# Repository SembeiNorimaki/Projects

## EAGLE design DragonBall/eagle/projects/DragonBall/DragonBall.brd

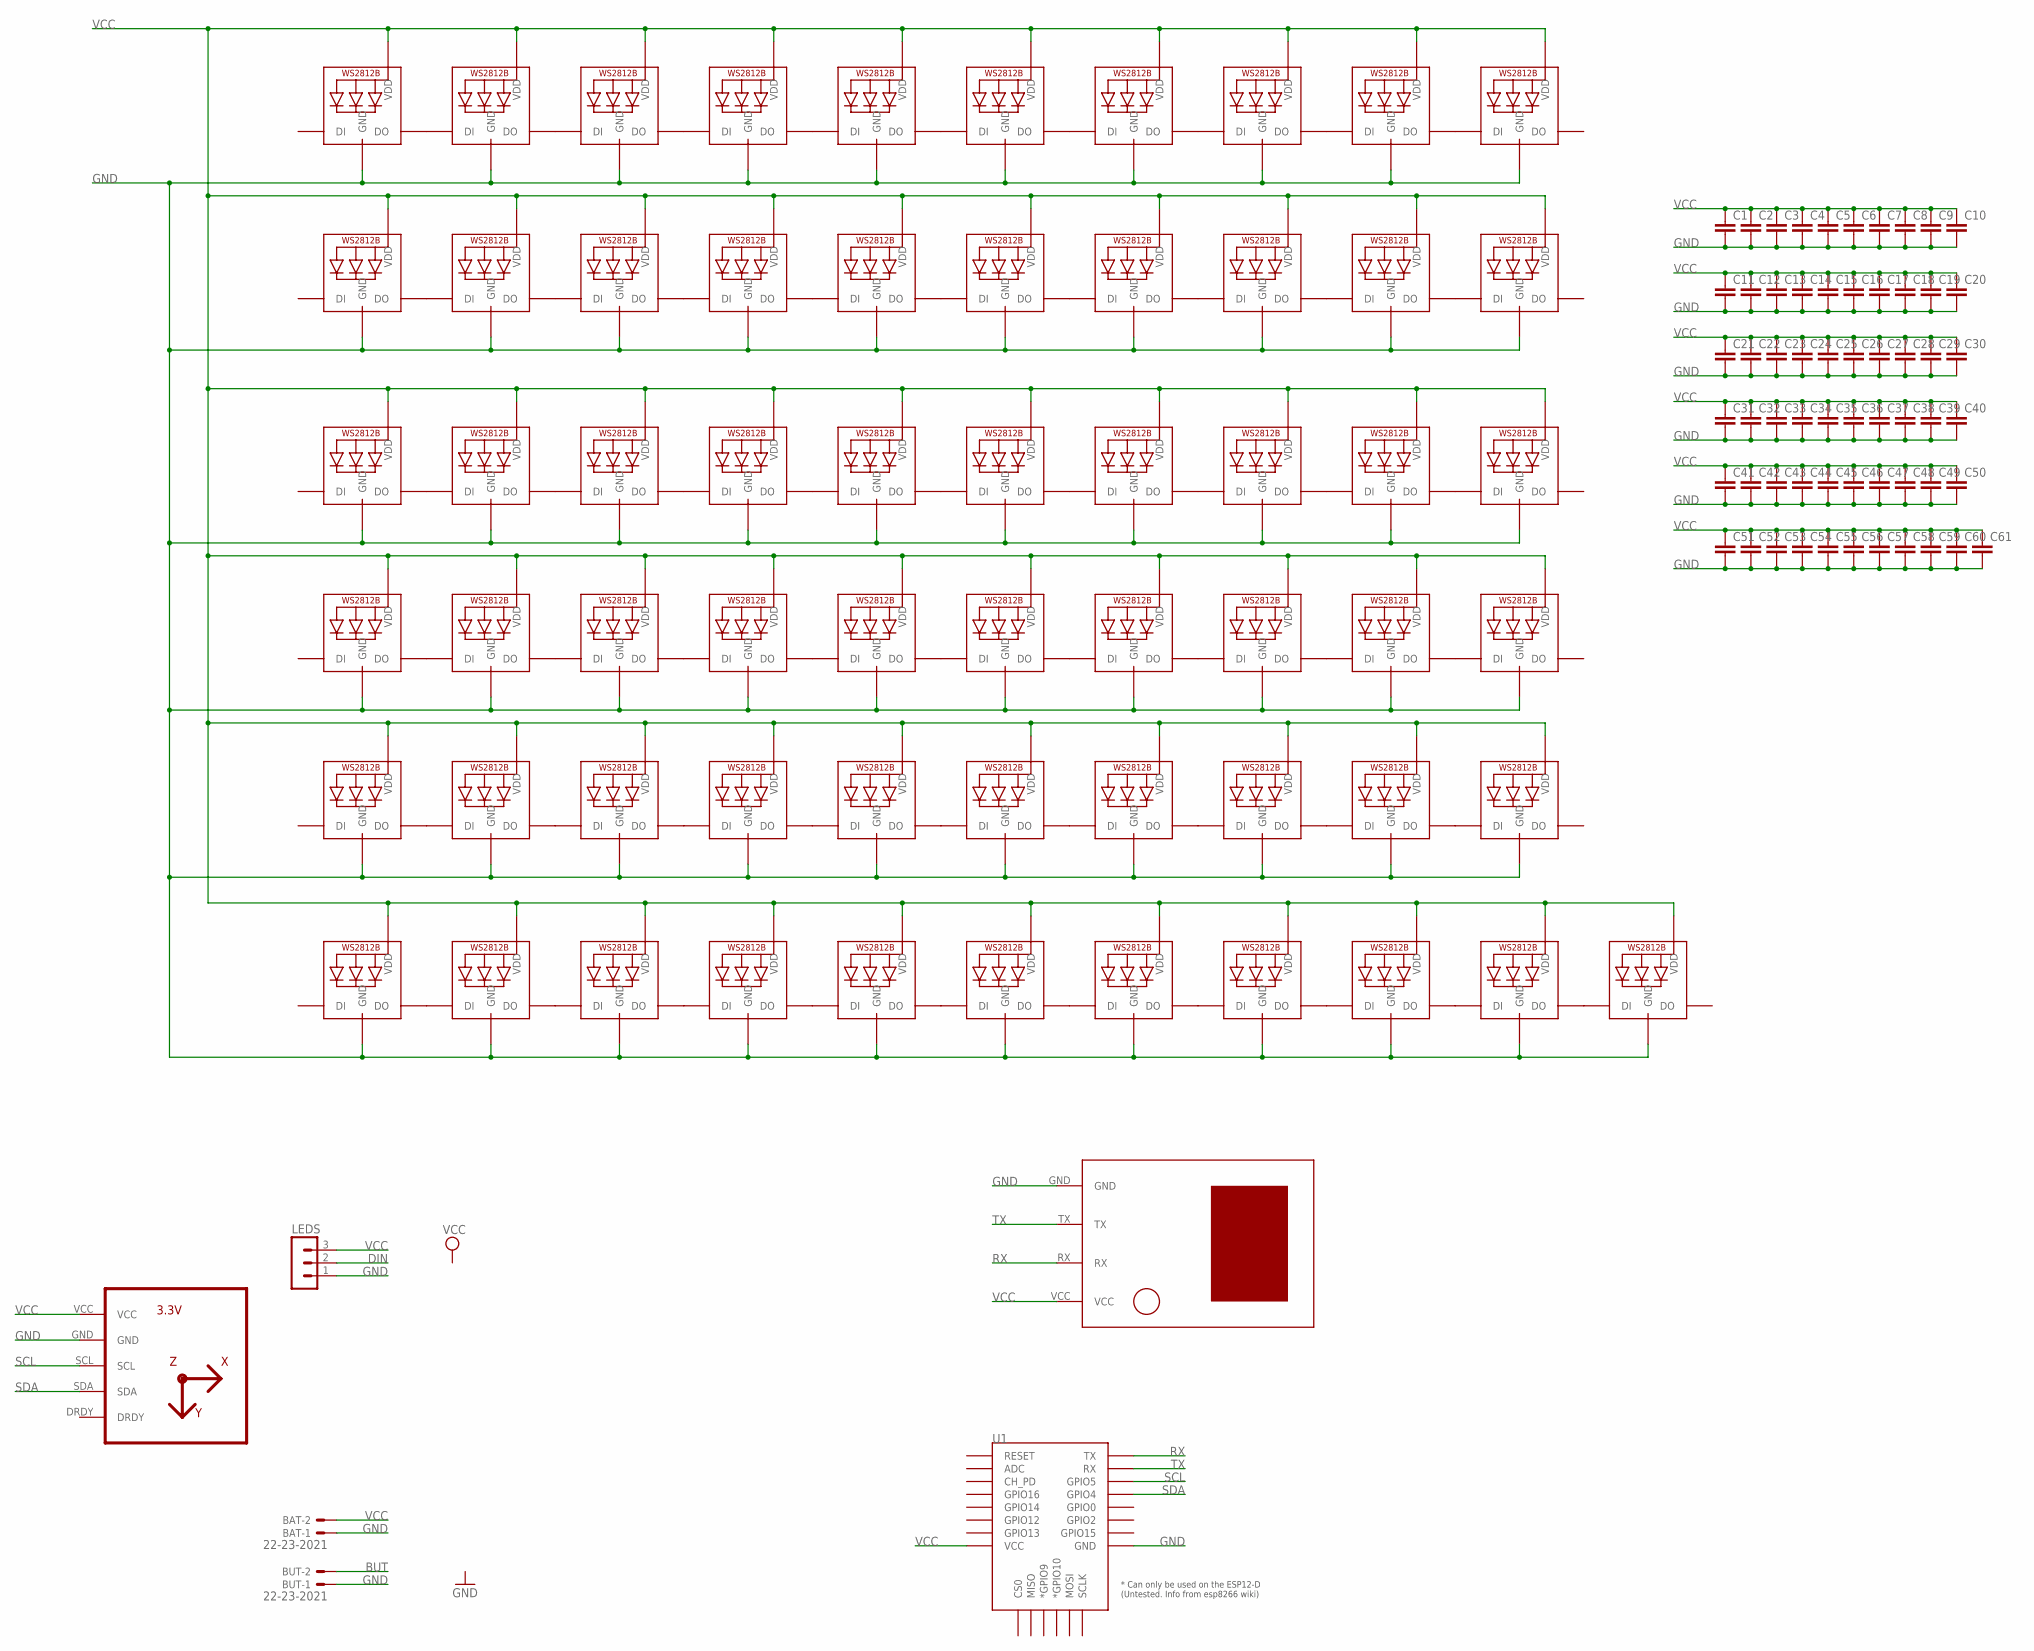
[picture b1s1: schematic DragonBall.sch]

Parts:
BAT: 22-23-2021
BUT: 22-23-2021
C1, C2, C3, C4, C5, C6, C7, C8, C9, C10, C11, C12, C13, C14, C15, C16, C17, C18, C19, C20, C21, C22, C23, C24, C25, C26, C27, C28, C29, C30, C31, C32, C33, C34, C35, C36, C37, C38, C39, C40, C41, C42, C43, C44, C45, C46, C47, C48, C49, C50, C51, C52, C53, C54, C55, C56, C57, C58, C59, C60, C61: C-EUC0402K; C0402K
GYRO: HMC5883LGY-271; GY-271
LED1, LED2, LED3, LED4, LED5, LED6, LED7, LED8, LED9, LED10, LED11, LED12, LED13, LED14, LED15, LED16, LED17, LED18, LED19, LED20, LED21, LED22, LED23, LED24, LED25, LED26, LED27, LED28, LED29, LED30, LED31, LED32, LED33, LED34, LED35, LED36, LED37, LED38, LED39, LED40, LED41, LED42, LED43, LED44, LED45, LED46, LED47, LED48, LED49, LED50, LED51, LED52, LED53, LED54, LED55, LED56, LED57, LED58, LED59, LED60, LED61: WS2812B_5050N; WS2812B-NARROW
LEDS: MA03-1
U1: ESP12ESMD; ESP12E-SMD
U$3: U-BLOX-NEO6V2

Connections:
BUT: BUT.2
DIN: LEDS.2
GND: BAT.1, BUT.1, C1.2, C2.2, C3.2, C4.2, C5.2, C6.2, C7.2, C8.2, C9.2, C10.2, C11.2, C12.2, C13.2, C14.2, C15.2, C16.2, C17.2, C18.2, C19.2, C20.2, C21.2, C22.2, C23.2, C24.2, C25.2, C26.2, C27.2, C28.2, C29.2, C30.2, C31.2, C32.2, C33.2, C34.2, C35.2, C36.2, C37.2, C38.2, C39.2, C40.2, C41.2, C42.2, C43.2, C44.2, C45.2, C46.2, C47.2, C48.2, C49.2, C50.2, C51.2, C52.2, C53.2, C54.2, C55.2, C56.2, C57.2, C58.2, C59.2, C60.2, C61.2, GYRO.GND, LED1.3-GND (GND), LED2.3-GND (GND), LED3.3-GND (GND), LED4.3-GND (GND), LED5.3-GND (GND), LED6.3-GND (GND), LED7.3-GND (GND), LED8.3-GND (GND), LED9.3-GND (GND), LED10.3-GND (GND), LED11.3-GND (GND), LED12.3-GND (GND), LED13.3-GND (GND), LED14.3-GND (GND), LED15.3-GND (GND), LED16.3-GND (GND), LED17.3-GND (GND), LED18.3-GND (GND), LED19.3-GND (GND), LED20.3-GND (GND), LED21.3-GND (GND), LED22.3-GND (GND), LED23.3-GND (GND), LED24.3-GND (GND), LED25.3-GND (GND), LED26.3-GND (GND), LED27.3-GND (GND), LED28.3-GND (GND), LED29.3-GND (GND), LED30.3-GND (GND), LED31.3-GND (GND), LED32.3-GND (GND), LED33.3-GND (GND), LED34.3-GND (GND), LED35.3-GND (GND), LED36.3-GND (GND), LED37.3-GND (GND), LED38.3-GND (GND), LED39.3-GND (GND), LED40.3-GND (GND), LED41.3-GND (GND), LED42.3-GND (GND), LED43.3-GND (GND), LED44.3-GND (GND), LED45.3-GND (GND), LED46.3-GND (GND), LED47.3-GND (GND), LED48.3-GND (GND), LED49.3-GND (GND), LED50.3-GND (GND), LED51.3-GND (GND), LED52.3-GND (GND), LED53.3-GND (GND), LED54.3-GND (GND), LED55.3-GND (GND), LED56.3-GND (GND), LED57.3-GND (GND), LED58.3-GND (GND), LED59.3-GND (GND), LED60.3-GND (GND), LED61.3-GND (GND), LEDS.1, U1.GND, U$3.GND
unnamed: LED1.2-DOUT (DO), LED2.4-DIN (DI)
unnamed: LED2.2-DOUT (DO), LED3.4-DIN (DI)
unnamed: LED3.2-DOUT (DO), LED4.4-DIN (DI)
unnamed: LED4.2-DOUT (DO), LED5.4-DIN (DI)
unnamed: LED5.2-DOUT (DO), LED6.4-DIN (DI)
unnamed: LED6.2-DOUT (DO), LED7.4-DIN (DI)
unnamed: LED7.2-DOUT (DO), LED8.4-DIN (DI)
unnamed: LED8.2-DOUT (DO), LED9.4-DIN (DI)
unnamed: LED9.2-DOUT (DO), LED10.4-DIN (DI)
unnamed: LED11.2-DOUT (DO), LED12.4-DIN (DI)
unnamed: LED12.2-DOUT (DO), LED13.4-DIN (DI)
unnamed: LED13.2-DOUT (DO), LED14.4-DIN (DI)
unnamed: LED14.2-DOUT (DO), LED15.4-DIN (DI)
unnamed: LED15.2-DOUT (DO), LED16.4-DIN (DI)
unnamed: LED16.2-DOUT (DO), LED17.4-DIN (DI)
unnamed: LED17.2-DOUT (DO), LED18.4-DIN (DI)
unnamed: LED18.2-DOUT (DO), LED19.4-DIN (DI)
unnamed: LED19.2-DOUT (DO), LED20.4-DIN (DI)
unnamed: LED21.2-DOUT (DO), LED22.4-DIN (DI)
unnamed: LED22.2-DOUT (DO), LED23.4-DIN (DI)
unnamed: LED23.2-DOUT (DO), LED24.4-DIN (DI)
unnamed: LED24.2-DOUT (DO), LED25.4-DIN (DI)
unnamed: LED25.2-DOUT (DO), LED26.4-DIN (DI)
unnamed: LED26.2-DOUT (DO), LED27.4-DIN (DI)
unnamed: LED27.2-DOUT (DO), LED28.4-DIN (DI)
unnamed: LED28.2-DOUT (DO), LED29.4-DIN (DI)
unnamed: LED29.2-DOUT (DO), LED30.4-DIN (DI)
unnamed: LED31.2-DOUT (DO), LED32.4-DIN (DI)
unnamed: LED32.2-DOUT (DO), LED33.4-DIN (DI)
unnamed: LED33.2-DOUT (DO), LED34.4-DIN (DI)
unnamed: LED34.2-DOUT (DO), LED35.4-DIN (DI)
unnamed: LED35.2-DOUT (DO), LED36.4-DIN (DI)
unnamed: LED36.2-DOUT (DO), LED37.4-DIN (DI)
unnamed: LED37.2-DOUT (DO), LED38.4-DIN (DI)
unnamed: LED38.2-DOUT (DO), LED39.4-DIN (DI)
unnamed: LED39.2-DOUT (DO), LED40.4-DIN (DI)
unnamed: LED41.2-DOUT (DO), LED42.4-DIN (DI)
unnamed: LED42.2-DOUT (DO), LED43.4-DIN (DI)
unnamed: LED43.2-DOUT (DO), LED44.4-DIN (DI)
unnamed: LED44.2-DOUT (DO), LED45.4-DIN (DI)
unnamed: LED45.2-DOUT (DO), LED46.4-DIN (DI)
unnamed: LED46.2-DOUT (DO), LED47.4-DIN (DI)
unnamed: LED47.2-DOUT (DO), LED48.4-DIN (DI)
unnamed: LED48.2-DOUT (DO), LED49.4-DIN (DI)
unnamed: LED49.2-DOUT (DO), LED50.4-DIN (DI)
unnamed: LED51.2-DOUT (DO), LED52.4-DIN (DI)
unnamed: LED52.2-DOUT (DO), LED53.4-DIN (DI)
unnamed: LED53.2-DOUT (DO), LED54.4-DIN (DI)
unnamed: LED54.2-DOUT (DO), LED55.4-DIN (DI)
unnamed: LED55.2-DOUT (DO), LED56.4-DIN (DI)
unnamed: LED56.2-DOUT (DO), LED57.4-DIN (DI)
unnamed: LED57.2-DOUT (DO), LED58.4-DIN (DI)
unnamed: LED58.2-DOUT (DO), LED59.4-DIN (DI)
unnamed: LED59.2-DOUT (DO), LED60.4-DIN (DI)
unnamed: LED60.2-DOUT (DO), LED61.4-DIN (DI)
RX: U1.TXD0 (TX), U$3.RX
SCL: GYRO.SCL, U1.GPIO5
SDA: GYRO.SDA, U1.GPIO4
TX: U1.RXD0 (RX), U$3.TX
VCC: BAT.2, C1.1, C2.1, C3.1, C4.1, C5.1, C6.1, C7.1, C8.1, C9.1, C10.1, C11.1, C12.1, C13.1, C14.1, C15.1, C16.1, C17.1, C18.1, C19.1, C20.1, C21.1, C22.1, C23.1, C24.1, C25.1, C26.1, C27.1, C28.1, C29.1, C30.1, C31.1, C32.1, C33.1, C34.1, C35.1, C36.1, C37.1, C38.1, C39.1, C40.1, C41.1, C42.1, C43.1, C44.1, C45.1, C46.1, C47.1, C48.1, C49.1, C50.1, C51.1, C52.1, C53.1, C54.1, C55.1, C56.1, C57.1, C58.1, C59.1, C60.1, C61.1, GYRO.VCC, LED1.1-VDD (VDD), LED2.1-VDD (VDD), LED3.1-VDD (VDD), LED4.1-VDD (VDD), LED5.1-VDD (VDD), LED6.1-VDD (VDD), LED7.1-VDD (VDD), LED8.1-VDD (VDD), LED9.1-VDD (VDD), LED10.1-VDD (VDD), LED11.1-VDD (VDD), LED12.1-VDD (VDD), LED13.1-VDD (VDD), LED14.1-VDD (VDD), LED15.1-VDD (VDD), LED16.1-VDD (VDD), LED17.1-VDD (VDD), LED18.1-VDD (VDD), LED19.1-VDD (VDD), LED20.1-VDD (VDD), LED21.1-VDD (VDD), LED22.1-VDD (VDD), LED23.1-VDD (VDD), LED24.1-VDD (VDD), LED25.1-VDD (VDD), LED26.1-VDD (VDD), LED27.1-VDD (VDD), LED28.1-VDD (VDD), LED29.1-VDD (VDD), LED30.1-VDD (VDD), LED31.1-VDD (VDD), LED32.1-VDD (VDD), LED33.1-VDD (VDD), LED34.1-VDD (VDD), LED35.1-VDD (VDD), LED36.1-VDD (VDD), LED37.1-VDD (VDD), LED38.1-VDD (VDD), LED39.1-VDD (VDD), LED40.1-VDD (VDD), LED41.1-VDD (VDD), LED42.1-VDD (VDD), LED43.1-VDD (VDD), LED44.1-VDD (VDD), LED45.1-VDD (VDD), LED46.1-VDD (VDD), LED47.1-VDD (VDD), LED48.1-VDD (VDD), LED49.1-VDD (VDD), LED50.1-VDD (VDD), LED51.1-VDD (VDD), LED52.1-VDD (VDD), LED53.1-VDD (VDD), LED54.1-VDD (VDD), LED55.1-VDD (VDD), LED56.1-VDD (VDD), LED57.1-VDD (VDD), LED58.1-VDD (VDD), LED59.1-VDD (VDD), LED60.1-VDD (VDD), LED61.1-VDD (VDD), LEDS.3, U1.VCC, U$3.VCC

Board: 2 copper layers, 128 parts (3 on the bottom side), 61 nets, no tracks yet.

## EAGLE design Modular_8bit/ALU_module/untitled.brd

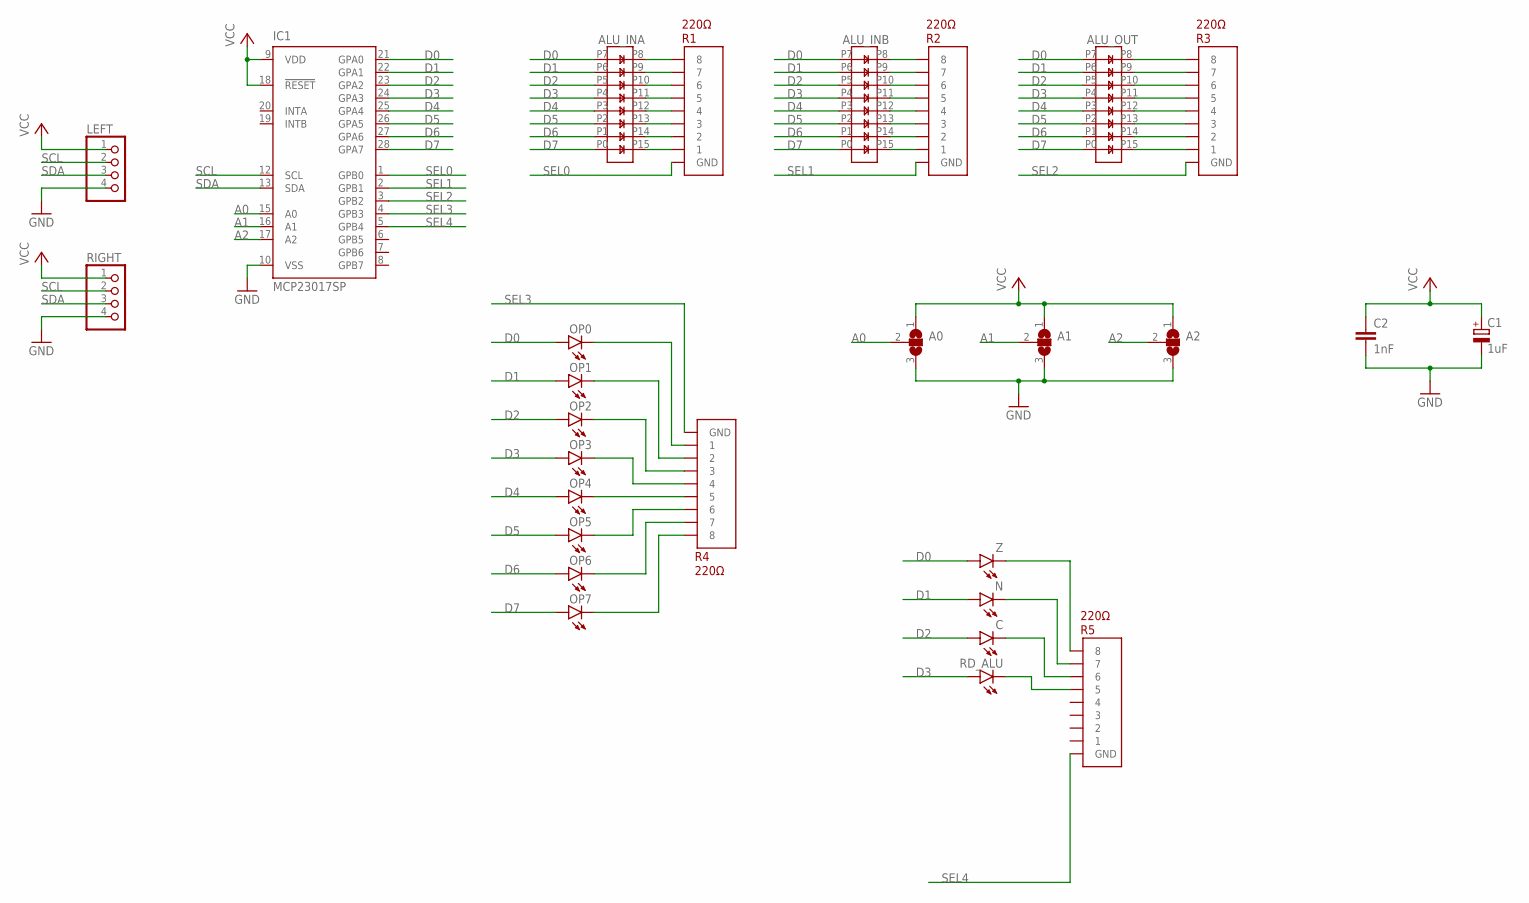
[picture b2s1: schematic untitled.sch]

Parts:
A0, A1, A2: SJ2W; SJ_2
ALU_INA: LB8
ALU_INB: LB8
ALU_OUT: LB8
C: LED3MM
C1: 1uF; E2,5-6
C2: 1nF; C2.5-2
IC1: MCP23017SP; DIL28-3
LEFT: PINHD-1X4; 1X04
N: LED3MM
OP0, OP1, OP2, OP3, OP4, OP5, OP6, OP7: LED3MM
R1, R2, R3, R4, R5: 220Ω; R_ARRAY_8PIN
RD_ALU: LED3MM
RIGHT: PINHD-1X4; 1X04
Z: LED3MM

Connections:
A0: A0.2, IC1.15 (A0)
A1: A1.2, IC1.16 (A1)
A2: A2.2, IC1.17 (A2)
D0: ALU_INA.P7, ALU_INB.P7, ALU_OUT.P7, IC1.21 (GPA0), OP0.A, Z.A
D1: ALU_INA.P6, ALU_INB.P6, ALU_OUT.P6, IC1.22 (GPA1), N.A, OP1.A
D2: ALU_INA.P5, ALU_INB.P5, ALU_OUT.P5, C.A, IC1.23 (GPA2), OP2.A
D3: ALU_INA.P4, ALU_INB.P4, ALU_OUT.P4, IC1.24 (GPA3), OP3.A, RD_ALU.A
D4: ALU_INA.P3, ALU_INB.P3, ALU_OUT.P3, IC1.25 (GPA4), OP4.A
D5: ALU_INA.P2, ALU_INB.P2, ALU_OUT.P2, IC1.26 (GPA5), OP5.A
D6: ALU_INA.P1, ALU_INB.P1, ALU_OUT.P1, IC1.27 (GPA6), OP6.A
D7: ALU_INA.P0, ALU_INB.P0, ALU_OUT.P0, IC1.28 (GPA7), OP7.A
GND: A0.3, A1.3, A2.3, C1.-, C2.2, IC1.10 (VSS), LEFT.4, RIGHT.4
unnamed: ALU_OUT.P8, R3.8
unnamed: ALU_OUT.P9, R3.7
unnamed: ALU_OUT.P10, R3.6
unnamed: ALU_OUT.P11, R3.5
unnamed: ALU_OUT.P12, R3.4
unnamed: ALU_OUT.P13, R3.3
unnamed: ALU_OUT.P14, R3.2
unnamed: ALU_OUT.P15, R3.1
unnamed: OP0.K (C), R4.1
unnamed: OP1.K (C), R4.2
unnamed: OP2.K (C), R4.3
unnamed: OP3.K (C), R4.4
unnamed: OP4.K (C), R4.5
unnamed: OP5.K (C), R4.6
unnamed: OP6.K (C), R4.7
unnamed: OP7.K (C), R4.8
unnamed: ALU_INA.P8, R1.8
unnamed: ALU_INA.P9, R1.7
unnamed: ALU_INA.P10, R1.6
unnamed: ALU_INA.P11, R1.5
unnamed: ALU_INA.P12, R1.4
unnamed: ALU_INA.P13, R1.3
unnamed: ALU_INA.P14, R1.2
unnamed: ALU_INA.P15, R1.1
unnamed: ALU_INB.P8, R2.8
unnamed: ALU_INB.P9, R2.7
unnamed: ALU_INB.P10, R2.6
unnamed: ALU_INB.P11, R2.5
unnamed: ALU_INB.P12, R2.4
unnamed: ALU_INB.P13, R2.3
unnamed: ALU_INB.P14, R2.2
unnamed: ALU_INB.P15, R2.1
unnamed: R5.8, Z.K (C)
unnamed: N.K (C), R5.7
unnamed: C.K (C), R5.6
unnamed: R5.5, RD_ALU.K (C)
SCL: IC1.12 (SCL), LEFT.2, RIGHT.2
SDA: IC1.13 (SDA), LEFT.3, RIGHT.3
SEL0: IC1.1 (GPB0), R1.GND
SEL1: IC1.2 (GPB1), R2.GND
SEL2: IC1.3 (GPB2), R3.GND
SEL3: IC1.4 (GPB3), R4.GND
SEL4: IC1.5 (GPB4), R5.GND
VCC: A0.1, A1.1, A2.1, C1.+, C2.1, IC1.9 (VDD), IC1.18 (!RESET), LEFT.1, RIGHT.1

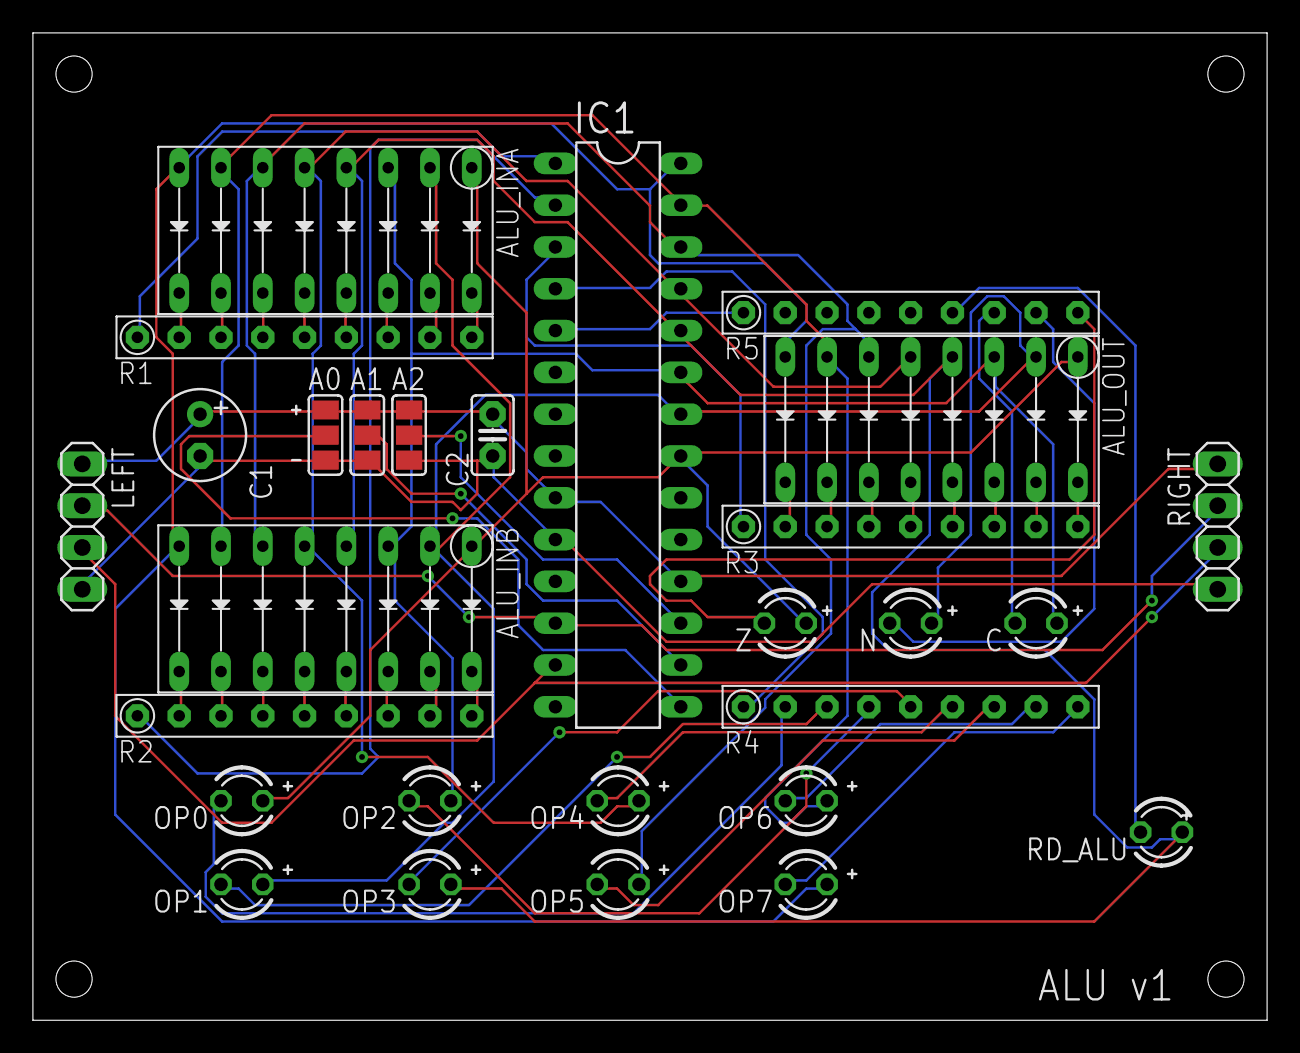
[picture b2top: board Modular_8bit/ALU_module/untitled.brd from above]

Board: 2 copper layers, 75.0 x 60.0 mm, 28 parts (0 on the bottom side), 56 nets.

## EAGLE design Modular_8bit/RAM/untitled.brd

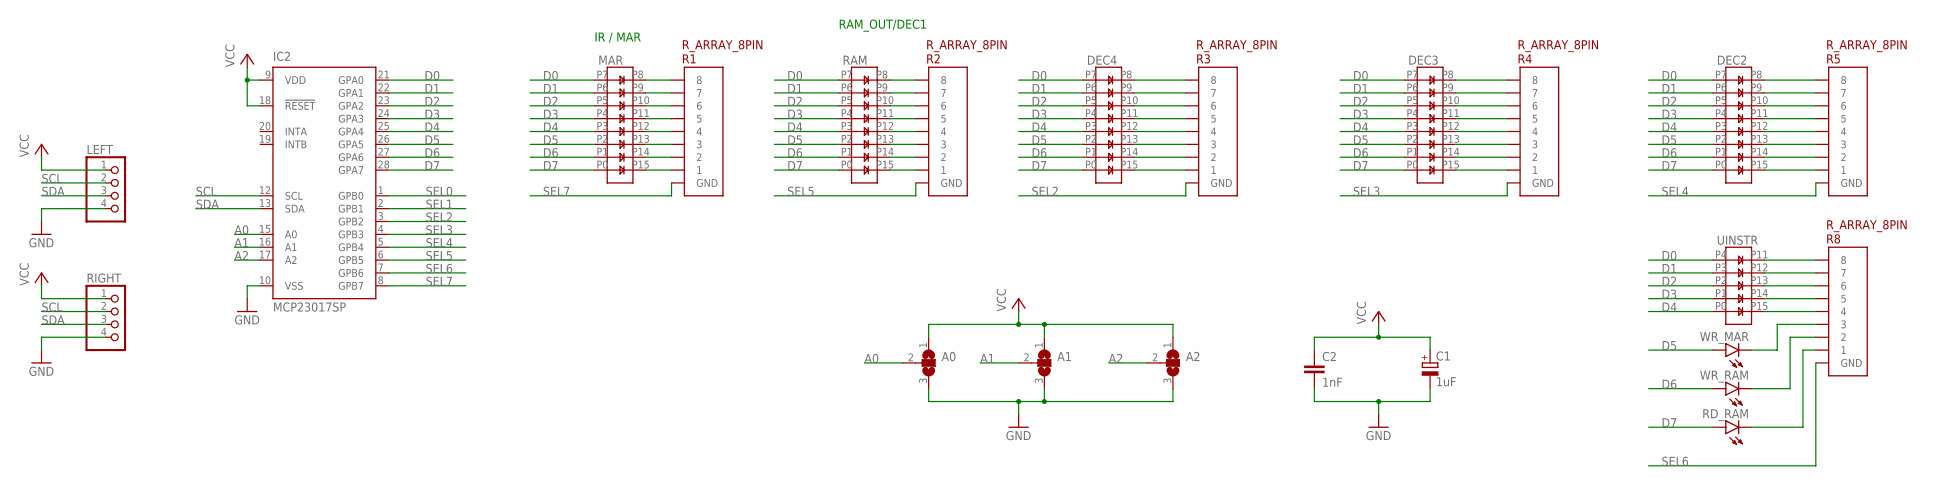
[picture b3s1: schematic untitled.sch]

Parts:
A0, A1, A2: SJ2W; SJ_2
C1: 1uF; E2,5-6
C2: 1nF; C2.5-2
DEC2, DEC3, DEC4: LB8
IC2: MCP23017SP; DIL28-3
LEFT: PINHD-1X4; 1X04
MAR: LB8
R1, R2, R3, R4, R5, R8: R_ARRAY_8PIN
RAM: LB8
RD_RAM: LED3MM
RIGHT: PINHD-1X4; 1X04
UINSTR: LB5
WR_MAR: LED3MM
WR_RAM: LED3MM

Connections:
A0: A0.2, IC2.15 (A0)
A1: A1.2, IC2.16 (A1)
A2: A2.2, IC2.17 (A2)
D0: DEC2.P7, DEC3.P7, DEC4.P7, IC2.21 (GPA0), MAR.P7, RAM.P7, UINSTR.P4
D1: DEC2.P6, DEC3.P6, DEC4.P6, IC2.22 (GPA1), MAR.P6, RAM.P6, UINSTR.P3
D2: DEC2.P5, DEC3.P5, DEC4.P5, IC2.23 (GPA2), MAR.P5, RAM.P5, UINSTR.P2
D3: DEC2.P4, DEC3.P4, DEC4.P4, IC2.24 (GPA3), MAR.P4, RAM.P4, UINSTR.P1
D4: DEC2.P3, DEC3.P3, DEC4.P3, IC2.25 (GPA4), MAR.P3, RAM.P3, UINSTR.P0
D5: DEC2.P2, DEC3.P2, DEC4.P2, IC2.26 (GPA5), MAR.P2, RAM.P2, WR_MAR.A
D6: DEC2.P1, DEC3.P1, DEC4.P1, IC2.27 (GPA6), MAR.P1, RAM.P1, WR_RAM.A
D7: DEC2.P0, DEC3.P0, DEC4.P0, IC2.28 (GPA7), MAR.P0, RAM.P0, RD_RAM.A
GND: A0.3, A1.3, A2.3, C1.-, C2.2, IC2.10 (VSS), LEFT.4, RIGHT.4
unnamed: DEC4.P8, R3.8
unnamed: DEC4.P9, R3.7
unnamed: DEC4.P10, R3.6
unnamed: DEC4.P11, R3.5
unnamed: DEC4.P12, R3.4
unnamed: DEC4.P13, R3.3
unnamed: DEC4.P14, R3.2
unnamed: DEC4.P15, R3.1
unnamed: R8.3, WR_MAR.K (C)
unnamed: R8.2, WR_RAM.K (C)
unnamed: R8.1, RD_RAM.K (C)
unnamed: MAR.P8, R1.8
unnamed: MAR.P9, R1.7
unnamed: MAR.P10, R1.6
unnamed: MAR.P11, R1.5
unnamed: MAR.P12, R1.4
unnamed: MAR.P13, R1.3
unnamed: MAR.P14, R1.2
unnamed: MAR.P15, R1.1
unnamed: R2.8, RAM.P8
unnamed: R2.7, RAM.P9
unnamed: R2.6, RAM.P10
unnamed: R2.5, RAM.P11
unnamed: R2.4, RAM.P12
unnamed: R2.3, RAM.P13
unnamed: R2.2, RAM.P14
unnamed: R2.1, RAM.P15
unnamed: DEC3.P8, R4.8
unnamed: DEC3.P9, R4.7
unnamed: DEC3.P10, R4.6
unnamed: DEC3.P11, R4.5
unnamed: DEC3.P12, R4.4
unnamed: DEC3.P13, R4.3
unnamed: DEC3.P14, R4.2
unnamed: DEC3.P15, R4.1
unnamed: DEC2.P8, R5.8
unnamed: DEC2.P9, R5.7
unnamed: DEC2.P10, R5.6
unnamed: DEC2.P11, R5.5
unnamed: DEC2.P12, R5.4
unnamed: DEC2.P13, R5.3
unnamed: DEC2.P14, R5.2
unnamed: DEC2.P15, R5.1
unnamed: R8.8, UINSTR.P11
unnamed: R8.7, UINSTR.P12
unnamed: R8.6, UINSTR.P13
unnamed: R8.5, UINSTR.P14
unnamed: R8.4, UINSTR.P15
SCL: IC2.12 (SCL), LEFT.2, RIGHT.2
SDA: IC2.13 (SDA), LEFT.3, RIGHT.3
SEL0: IC2.1 (GPB0)
SEL1: IC2.2 (GPB1)
SEL2: IC2.3 (GPB2), R3.GND
SEL3: IC2.4 (GPB3), R4.GND
SEL4: IC2.5 (GPB4), R5.GND
SEL5: IC2.6 (GPB5), R2.GND
SEL6: IC2.7 (GPB6), R8.GND
SEL7: IC2.8 (GPB7), R1.GND
VCC: A0.1, A1.1, A2.1, C1.+, C2.1, IC2.9 (VDD), IC2.18 (!RESET), LEFT.1, RIGHT.1

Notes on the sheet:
IR / MAR
RAM_OUT/DEC1

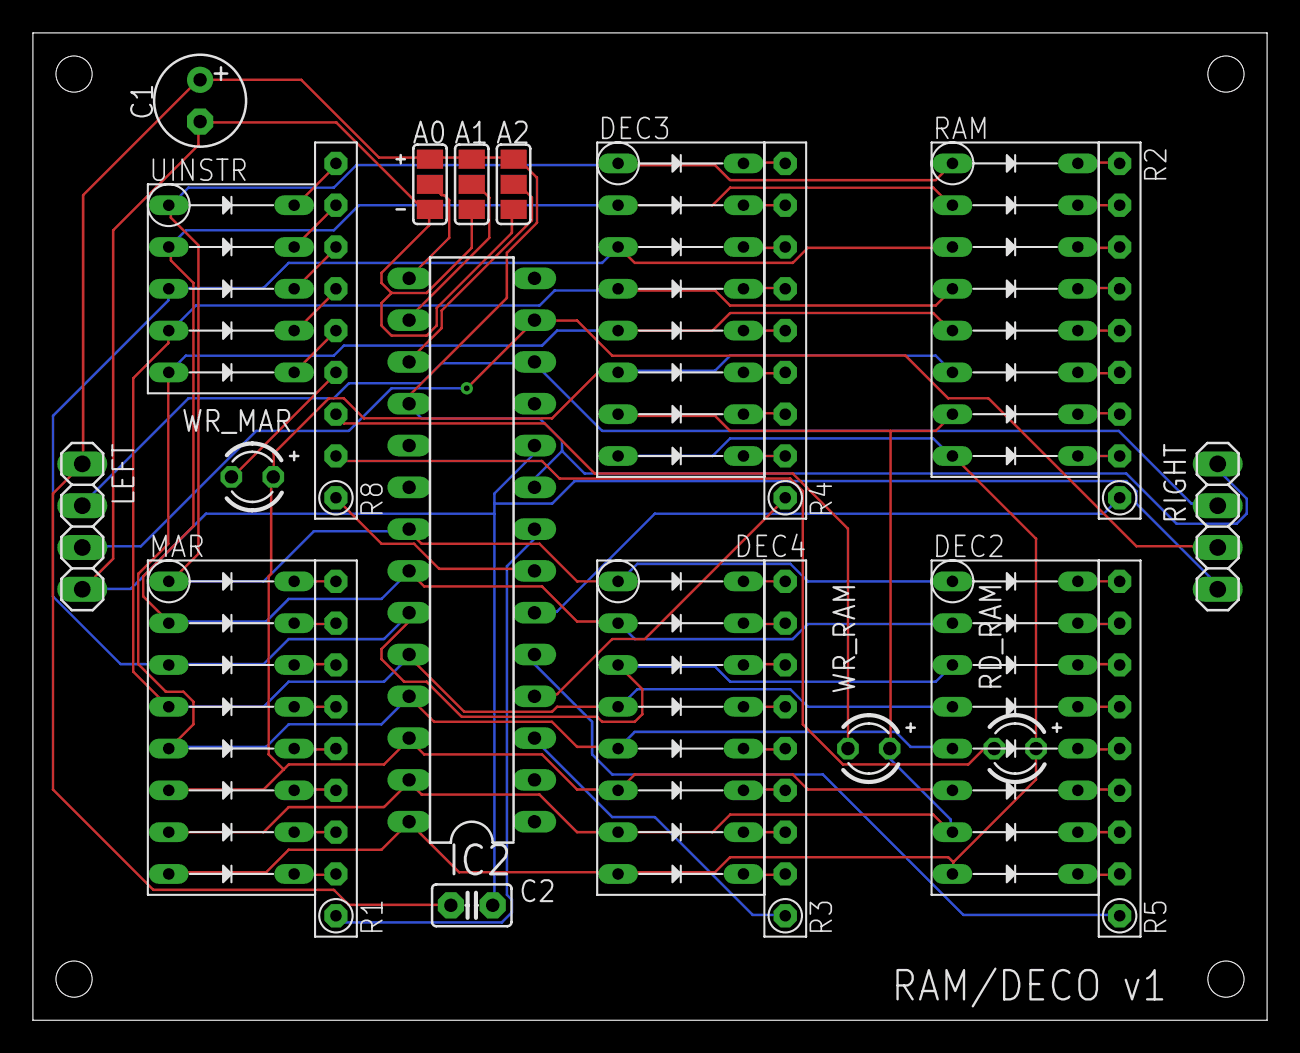
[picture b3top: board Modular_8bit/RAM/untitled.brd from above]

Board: 2 copper layers, 75.0 x 60.0 mm, 23 parts (0 on the bottom side), 69 nets.
